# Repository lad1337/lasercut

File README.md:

# Lasercut

PCB and case for an "iso" 72 key mechanical keyboard

## Layout

http://www.keyboard-layout-editor.com/#/gists/ba62eb48125304c6f380ac636846d038

## Case

The case is a sandwich style.
The plates can be rendered at http://builder.swillkb.com/
which is based on https://github.com/swill/kad.

in the case folder you will find a small go app(source) that can achive the same.

prerequisite:
    
    brew install inkscape pstoedit

render:

    cd case
    go run main.go

This will render svg, eps and dxf files.
These can be used with any CAD software.

You will need the following plates:

- 1x switch plate in 1.5mm
- 1x closed with magnets inserts in 3mm (not automatically rendered!!)
- 2x closed in 3mm
- 1x switch in 1.5mm
- 1x open in 3mm
- 1x bottom in 1-3mm

Example render in fusion with stainless steel and brass

## PCB

### Board edge

add the generated `./case/Lasercut_bottom.dxf` to the board and position:

    x: 23.0
    y: 19.94769

TODO: mounting holes

### Netlist

prerequisite: 

- `kle2netlist` installed, see https://github.com/lad1337/kle2netlist
    this will create a netlist from the kle json
- `kicad-kbplacer` kicad plugin installed, see https://github.com/lad1337/kicad-kbplacer
    this is a plugin that will place the swiches to the right place as well as create some tracks
- `node` and `npm install @ijprest/kle-serial --save` 
    this is needed for converting the kle json to its internal format

Steps:

- run:
    `make netlist`
- import the netlist into pcbnew
- run the kicad-kbplacer plugin
- rearrage the controller

    ```
    x: 335.4
    y: 72.6
    roation: 180
    ```
- finish all the other tracks

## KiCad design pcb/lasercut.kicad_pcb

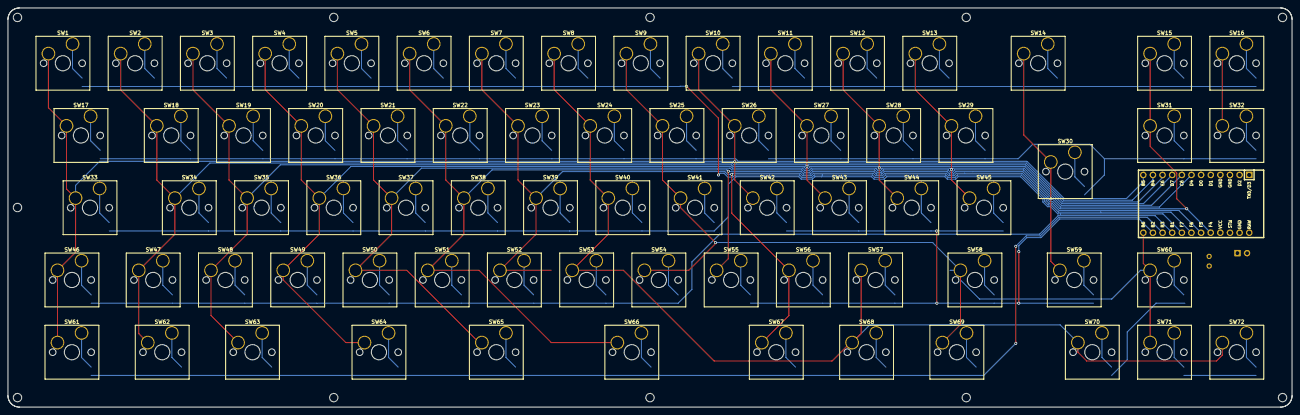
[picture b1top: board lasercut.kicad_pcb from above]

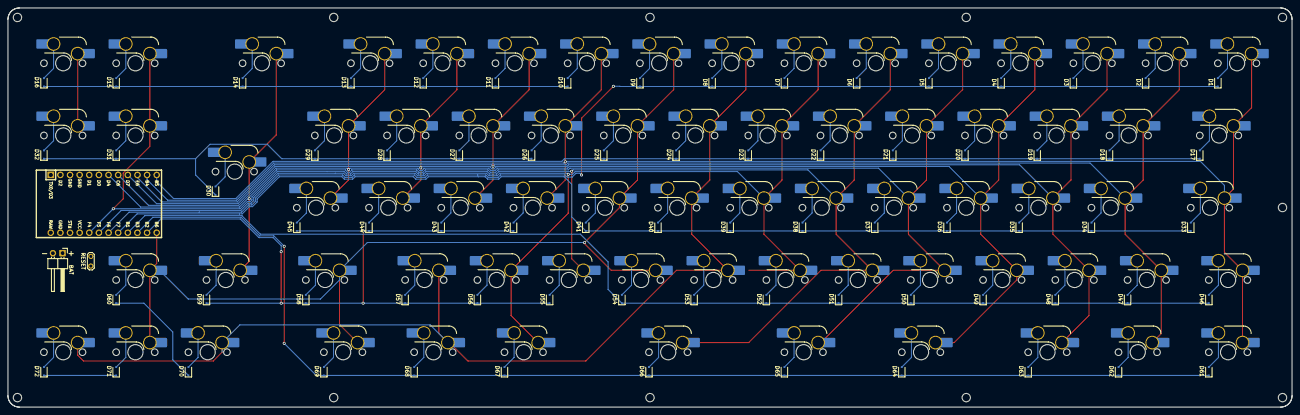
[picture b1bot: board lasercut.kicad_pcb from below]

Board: 2 copper layers, 338.6 x 105.3 mm, 147 parts (74 on the bottom side), 92 nets.

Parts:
BAT: PinHeader_1x02_P2.54mm_Horizontal
D1, D2, D3, D4, D5, D6, D7, D8, D9, D10, D11, D12, D13, D14, D15, D16, D17, D18, D19, D20, D21, D22, D23, D24, D25, D26, D27, D28, D29, D31, D32, D33, D34, D35, D36, D37, D38, D39, D40, D41, D42, D43, D44, D45, D46, D47, D48, D49, D50, D51, D52, D53, D54, D55, D56, D57, D58, D59, D60, D61, D62, D63, D64, D65, D66, D67, D68, D69, D70, D71, D72: 1N4148WS; D_SOD-323F
D30: D; D_SOD-323F
RESET: TestPoint_2Pads_Pitch2.54mm_Drill0.8mm
SW1, SW2, SW3, SW4, SW5, SW6, SW7, SW8, SW9, SW10, SW11, SW12, SW13, SW15, SW16, SW18, SW19, SW20, SW21, SW22, SW23, SW24, SW25, SW26, SW27, SW28, SW29, SW31, SW32, SW34, SW35, SW36, SW37, SW38, SW39, SW40, SW41, SW42, SW43, SW44, SW45, SW47, SW48, SW49, SW50, SW51, SW52, SW53, SW54, SW55, SW56, SW57, SW59, SW60, SW65, SW70, SW71, SW72: SW_Push; SW_Hotswap_Kailh_MX_plated_1.00u
SW14: SW_Push; SW_Hotswap_Kailh_MX_plated_2.00u
SW17: SW_Push; SW_Hotswap_Kailh_MX_plated_1.50u
SW30: SW_Push; SW_Hotswap_Kailh_MX_plated_ISOEnter
SW33, SW58: SW_Push; SW_Hotswap_Kailh_MX_plated_1.75u
SW46, SW61, SW62, SW63, SW67, SW68, SW69: SW_Push; SW_Hotswap_Kailh_MX_plated_1.25u
SW64: SW_Push; SW_Hotswap_Kailh_MX_plated_2.25u
SW66: SW_Push; SW_Hotswap_Kailh_MX_plated_2.75u
U: ProMicro; ArduinoProMicro

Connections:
BAT: BAT.1, U.24
COL0: SW1.1, SW10.1, SW17.1, SW26.1, SW33.1, SW42.1, SW46.1, SW61.1, U.11
COL1: SW2.1, SW11.1, SW18.1, SW27.1, SW34.1, SW43.1, SW47.1, SW62.1, U.10
COL2: SW3.1, SW12.1, SW19.1, SW28.1, SW35.1, SW44.1, SW48.1, SW63.1, U.9
COL3: SW4.1, SW13.1, SW20.1, SW29.1, SW36.1, SW45.1, SW49.1, SW64.1, U.8
COL4: SW5.1, SW14.1, SW21.1, SW30.1, SW37.1, SW50.1, SW59.1, SW65.1, U.7
COL5: SW6.1, SW15.1, SW22.1, SW31.1, SW38.1, SW51.1, SW55.1, SW66.1, U.20
COL6: SW7.1, SW16.1, SW23.1, SW32.1, SW39.1, SW52.1, SW56.1, SW67.1, U.19
COL7: SW8.1, SW24.1, SW40.1, SW53.1, SW57.1, SW68.1, SW70.1, SW72.1, U.2
COL8: SW9.1, SW25.1, SW41.1, SW54.1, SW58.1, SW60.1, SW69.1, SW71.1, U.13
GND: BAT.2, RESET.1, U.3, U.4, U.23
unnamed: D1.2, SW1.2
unnamed: D2.2, SW2.2
unnamed: D3.2, SW3.2
unnamed: D4.2, SW4.2
unnamed: D5.2, SW5.2
unnamed: D6.2, SW6.2
unnamed: D7.2, SW7.2
unnamed: D8.2, SW8.2
unnamed: D9.2, SW9.2
unnamed: D10.2, SW10.2
unnamed: D11.2, SW11.2
unnamed: D12.2, SW12.2
unnamed: D13.2, SW13.2
unnamed: D14.2, SW14.2
unnamed: D15.2, SW15.2
unnamed: D16.2, SW16.2
unnamed: D17.2, SW17.2
unnamed: D18.2, SW18.2
unnamed: D19.2, SW19.2
unnamed: D20.2, SW20.2
unnamed: D21.2, SW21.2
unnamed: D22.2, SW22.2
unnamed: D23.2, SW23.2
unnamed: D24.2, SW24.2
unnamed: D25.2, SW25.2
unnamed: D26.2, SW26.2
unnamed: D27.2, SW27.2
unnamed: D28.2, SW28.2
unnamed: D29.2, SW29.2
unnamed: D30.2, SW30.2
unnamed: D31.2, SW31.2
unnamed: D32.2, SW32.2
unnamed: D33.2, SW33.2
unnamed: D34.2, SW34.2
unnamed: D35.2, SW35.2
unnamed: D36.2, SW36.2
unnamed: D37.2, SW37.2
unnamed: D38.2, SW38.2
unnamed: D39.2, SW39.2
unnamed: D40.2, SW40.2
unnamed: D41.2, SW41.2
unnamed: D42.2, SW42.2
unnamed: D43.2, SW43.2
unnamed: D44.2, SW44.2
unnamed: D45.2, SW45.2
unnamed: D46.2, SW46.2
unnamed: D47.2, SW47.2
unnamed: D48.2, SW48.2
unnamed: D49.2, SW49.2
unnamed: D50.2, SW50.2
unnamed: D51.2, SW51.2
unnamed: D52.2, SW52.2
unnamed: D53.2, SW53.2
unnamed: D54.2, SW54.2
unnamed: D55.2, SW55.2
unnamed: D56.2, SW56.2
unnamed: D57.2, SW57.2
unnamed: D58.2, SW58.2
unnamed: D59.2, SW59.2
unnamed: D60.2, SW60.2
unnamed: D61.2, SW61.2
unnamed: D62.2, SW62.2
unnamed: D63.2, SW63.2
unnamed: D64.2, SW64.2
unnamed: D65.2, SW65.2
unnamed: D66.2, SW66.2
unnamed: D67.2, SW67.2
unnamed: D68.2, SW68.2
unnamed: D69.2, SW69.2
unnamed: D70.2, SW70.2
unnamed: D71.2, SW71.2
unnamed: D72.2, SW72.2
ROW0: D1.1, D2.1, D3.1, D4.1, D5.1, D6.1, D7.1, D8.1, D9.1, U.18
ROW1: D17.1, D18.1, D19.1, D20.1, D21.1, D22.1, D23.1, D24.1, D25.1, U.12
ROW2: D33.1, D34.1, D35.1, D36.1, D37.1, D38.1, D39.1, D40.1, D41.1, U.17
ROW3: D46.1, D47.1, D48.1, D49.1, D50.1, D51.1, D52.1, D53.1, D54.1, U.16
ROW4: D61.1, D62.1, D63.1, D64.1, D65.1, D66.1, D67.1, D68.1, D69.1, U.15
ROW5: D10.1, D11.1, D12.1, D13.1, D14.1, D15.1, D16.1, D60.1, D70.1
ROW6: D26.1, D27.1, D28.1, D29.1, D30.1, D31.1, D32.1, D71.1, D72.1, U.6
ROW7: D42.1, D43.1, D44.1, D45.1, D55.1, D56.1, D57.1, D58.1, D59.1, U.14
RST: RESET.2, U.22

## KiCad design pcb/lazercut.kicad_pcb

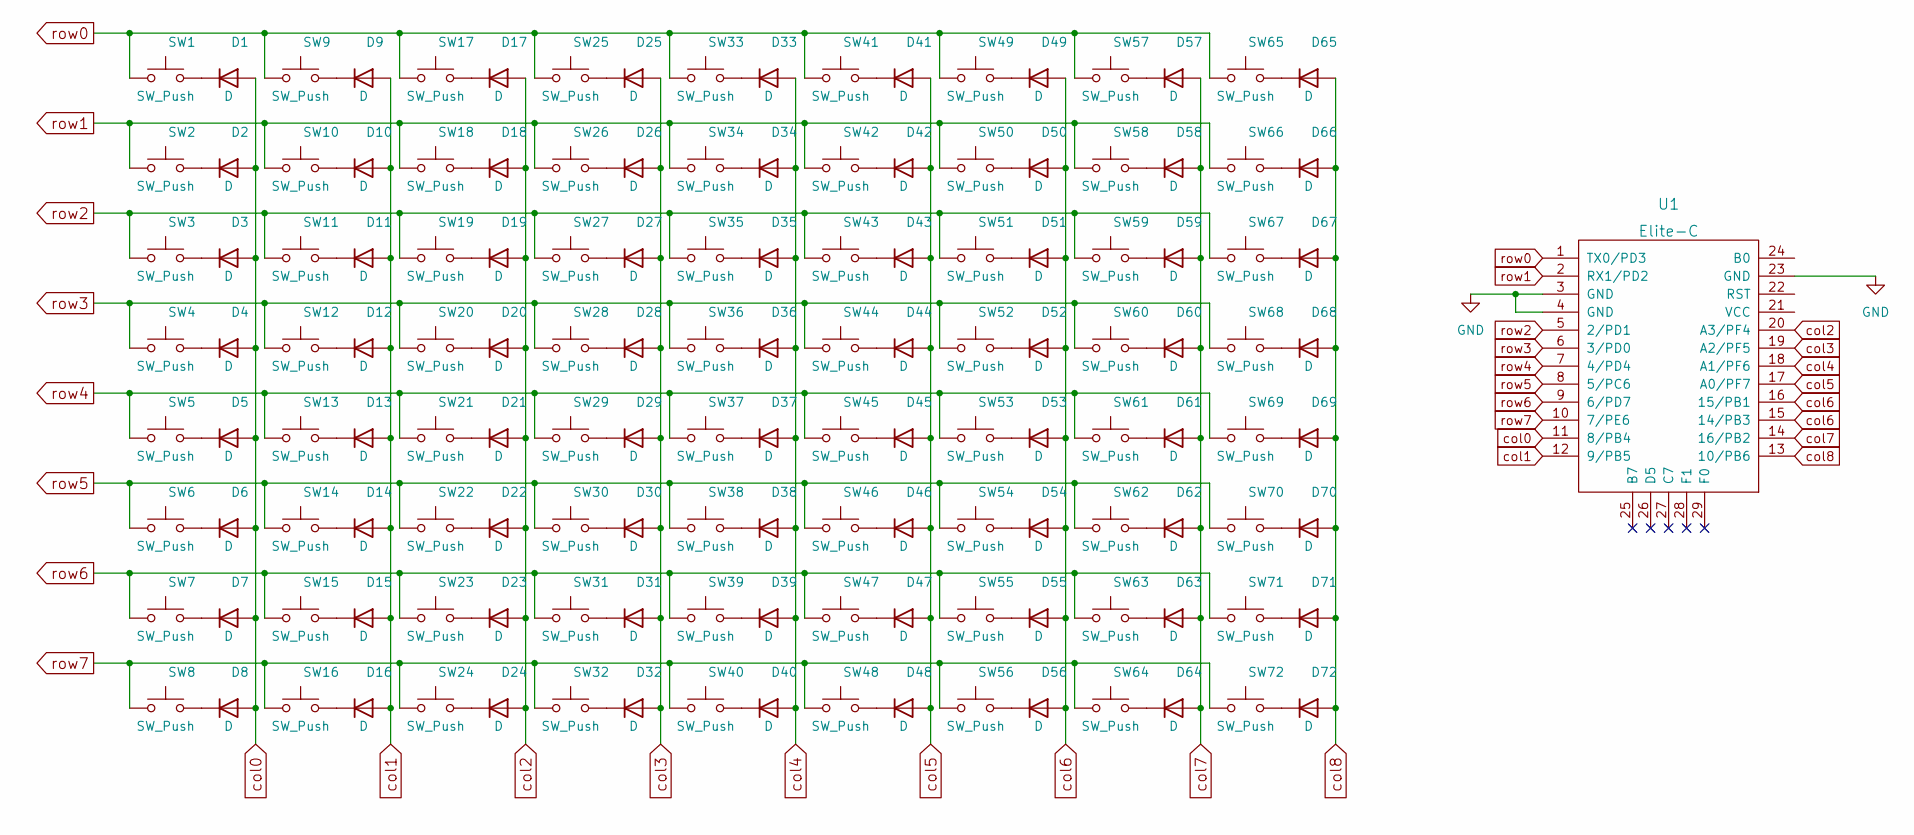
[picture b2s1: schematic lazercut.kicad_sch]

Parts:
D1, D2, D3, D4, D5, D6, D7, D8, D9, D10, D11, D12, D13, D14, D15, D16, D17, D18, D19, D20, D21, D22, D23, D24, D25, D26, D27, D28, D29, D30, D31, D32, D33, D34, D35, D36, D37, D38, D39, D40, D41, D42, D43, D44, D45, D46, D47, D48, D49, D50, D51, D52, D53, D54, D55, D56, D57, D58, D59, D60, D61, D62, D63, D64, D65, D66, D67, D68, D69, D70, D71, D72: D; D_SOD-128
SW1, SW2, SW3, SW4, SW5, SW6, SW7, SW8, SW9, SW10, SW11, SW12, SW13, SW14, SW15, SW16, SW17, SW18, SW19, SW20, SW21, SW22, SW23, SW24, SW25, SW26, SW27, SW28, SW29, SW30, SW31, SW32, SW33, SW34, SW35, SW36, SW37, SW38, SW39, SW40, SW41, SW42, SW43, SW44, SW45, SW46, SW47, SW48, SW49, SW50, SW51, SW52, SW53, SW54, SW55, SW56, SW57, SW58, SW59, SW60, SW61, SW62, SW63, SW64, SW65, SW66, SW67, SW68, SW69, SW70, SW71, SW72: SW_Push; MXOnly-1U-Hotswap-Antishear
U1: Elite-C

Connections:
GND: U1.3 (GND), U1.4 (GND), U1.23 (GND)
unnamed: D1.1 (K), SW1.2
unnamed: D2.1 (K), SW2.2
unnamed: D3.1 (K), SW3.2
unnamed: D4.1 (K), SW4.2
unnamed: D5.1 (K), SW5.2
unnamed: D6.1 (K), SW6.2
unnamed: D7.1 (K), SW7.2
unnamed: D8.1 (K), SW8.2
unnamed: D9.1 (K), SW9.2
unnamed: D10.1 (K), SW10.2
unnamed: D11.1 (K), SW11.2
unnamed: D12.1 (K), SW12.2
unnamed: D13.1 (K), SW13.2
unnamed: D14.1 (K), SW14.2
unnamed: D15.1 (K), SW15.2
unnamed: D16.1 (K), SW16.2
unnamed: D17.1 (K), SW17.2
unnamed: D18.1 (K), SW18.2
unnamed: D19.1 (K), SW19.2
unnamed: D20.1 (K), SW20.2
unnamed: D21.1 (K), SW21.2
unnamed: D22.1 (K), SW22.2
unnamed: D23.1 (K), SW23.2
unnamed: D24.1 (K), SW24.2
unnamed: D25.1 (K), SW25.2
unnamed: D26.1 (K), SW26.2
unnamed: D27.1 (K), SW27.2
unnamed: D28.1 (K), SW28.2
unnamed: D29.1 (K), SW29.2
unnamed: D30.1 (K), SW30.2
unnamed: D31.1 (K), SW31.2
unnamed: D32.1 (K), SW32.2
unnamed: D33.1 (K), SW33.2
unnamed: D34.1 (K), SW34.2
unnamed: D35.1 (K), SW35.2
unnamed: D36.1 (K), SW36.2
unnamed: D37.1 (K), SW37.2
unnamed: D38.1 (K), SW38.2
unnamed: D39.1 (K), SW39.2
unnamed: D40.1 (K), SW40.2
unnamed: D41.1 (K), SW41.2
unnamed: D42.1 (K), SW42.2
unnamed: D43.1 (K), SW43.2
unnamed: D44.1 (K), SW44.2
unnamed: D45.1 (K), SW45.2
unnamed: D46.1 (K), SW46.2
unnamed: D47.1 (K), SW47.2
unnamed: D48.1 (K), SW48.2
unnamed: D49.1 (K), SW49.2
unnamed: D50.1 (K), SW50.2
unnamed: D51.1 (K), SW51.2
unnamed: D52.1 (K), SW52.2
unnamed: D53.1 (K), SW53.2
unnamed: D54.1 (K), SW54.2
unnamed: D55.1 (K), SW55.2
unnamed: D56.1 (K), SW56.2
unnamed: D57.1 (K), SW57.2
unnamed: D58.1 (K), SW58.2
unnamed: D59.1 (K), SW59.2
unnamed: D60.1 (K), SW60.2
unnamed: D61.1 (K), SW61.2
unnamed: D62.1 (K), SW62.2
unnamed: D63.1 (K), SW63.2
unnamed: D64.1 (K), SW64.2
unnamed: D65.1 (K), SW65.2
unnamed: D66.1 (K), SW66.2
unnamed: D67.1 (K), SW67.2
unnamed: D68.1 (K), SW68.2
unnamed: D69.1 (K), SW69.2
unnamed: D70.1 (K), SW70.2
unnamed: D71.1 (K), SW71.2
unnamed: D72.1 (K), SW72.2
col0: D1.2 (A), D2.2 (A), D3.2 (A), D4.2 (A), D5.2 (A), D6.2 (A), D7.2 (A), D8.2 (A), U1.11 (8/PB4)
col1: D9.2 (A), D10.2 (A), D11.2 (A), D12.2 (A), D13.2 (A), D14.2 (A), D15.2 (A), D16.2 (A), U1.12 (9/PB5)
col2: D17.2 (A), D18.2 (A), D19.2 (A), D20.2 (A), D21.2 (A), D22.2 (A), D23.2 (A), D24.2 (A), U1.20 (A3/PF4)
col3: D25.2 (A), D26.2 (A), D27.2 (A), D28.2 (A), D29.2 (A), D30.2 (A), D31.2 (A), D32.2 (A), U1.19 (A2/PF5)
col4: D33.2 (A), D34.2 (A), D35.2 (A), D36.2 (A), D37.2 (A), D38.2 (A), D39.2 (A), D40.2 (A), U1.18 (A1/PF6)
col5: D41.2 (A), D42.2 (A), D43.2 (A), D44.2 (A), D45.2 (A), D46.2 (A), D47.2 (A), D48.2 (A), U1.17 (A0/PF7)
col6: D49.2 (A), D50.2 (A), D51.2 (A), D52.2 (A), D53.2 (A), D54.2 (A), D55.2 (A), D56.2 (A), U1.15 (14/PB3), U1.16 (15/PB1)
col7: D57.2 (A), D58.2 (A), D59.2 (A), D60.2 (A), D61.2 (A), D62.2 (A), D63.2 (A), D64.2 (A), U1.14 (16/PB2)
col8: D65.2 (A), D66.2 (A), D67.2 (A), D68.2 (A), D69.2 (A), D70.2 (A), D71.2 (A), D72.2 (A), U1.13 (10/PB6)
row0: SW1.1, SW9.1, SW17.1, SW25.1, SW33.1, SW41.1, SW49.1, SW57.1, SW65.1, U1.1 (TX0/PD3)
row1: SW2.1, SW10.1, SW18.1, SW26.1, SW34.1, SW42.1, SW50.1, SW58.1, SW66.1, U1.2 (RX1/PD2)
row2: SW3.1, SW11.1, SW19.1, SW27.1, SW35.1, SW43.1, SW51.1, SW59.1, SW67.1, U1.5 (2/PD1)
row3: SW4.1, SW12.1, SW20.1, SW28.1, SW36.1, SW44.1, SW52.1, SW60.1, SW68.1, U1.6 (3/PD0)
row4: SW5.1, SW13.1, SW21.1, SW29.1, SW37.1, SW45.1, SW53.1, SW61.1, SW69.1, U1.7 (4/PD4)
row5: SW6.1, SW14.1, SW22.1, SW30.1, SW38.1, SW46.1, SW54.1, SW62.1, SW70.1, U1.8 (5/PC6)
row6: SW7.1, SW15.1, SW23.1, SW31.1, SW39.1, SW47.1, SW55.1, SW63.1, SW71.1, U1.9 (6/PD7)
row7: SW8.1, SW16.1, SW24.1, SW32.1, SW40.1, SW48.1, SW56.1, SW64.1, SW72.1, U1.10 (7/PE6)

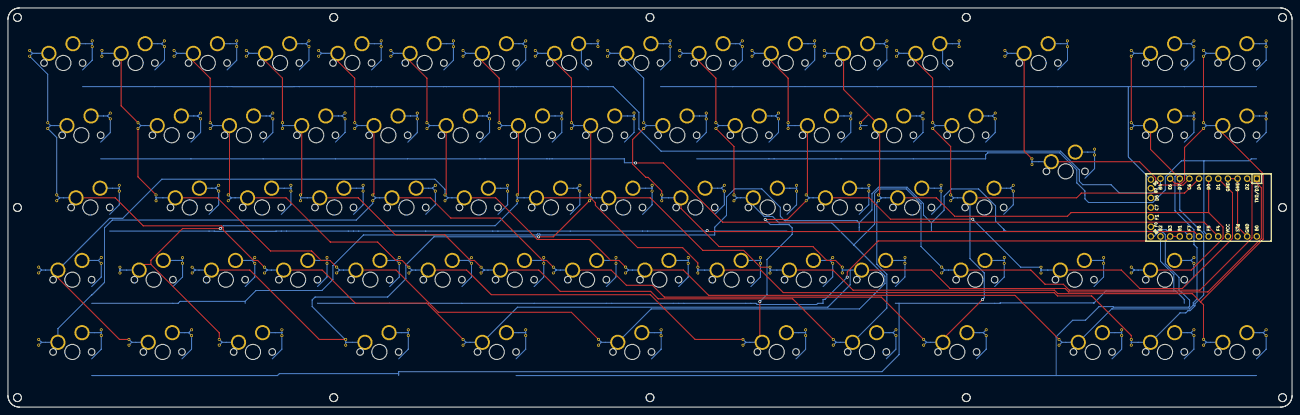
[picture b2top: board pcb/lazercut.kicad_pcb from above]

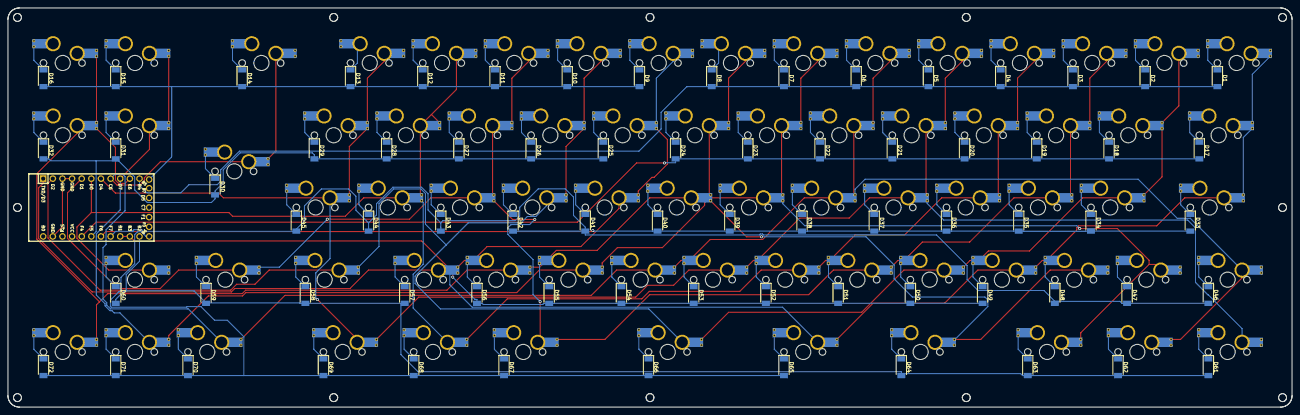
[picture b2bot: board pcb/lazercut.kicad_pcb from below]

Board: 2 copper layers, 338.6 x 105.3 mm, 145 parts (72 on the bottom side), 90 nets.

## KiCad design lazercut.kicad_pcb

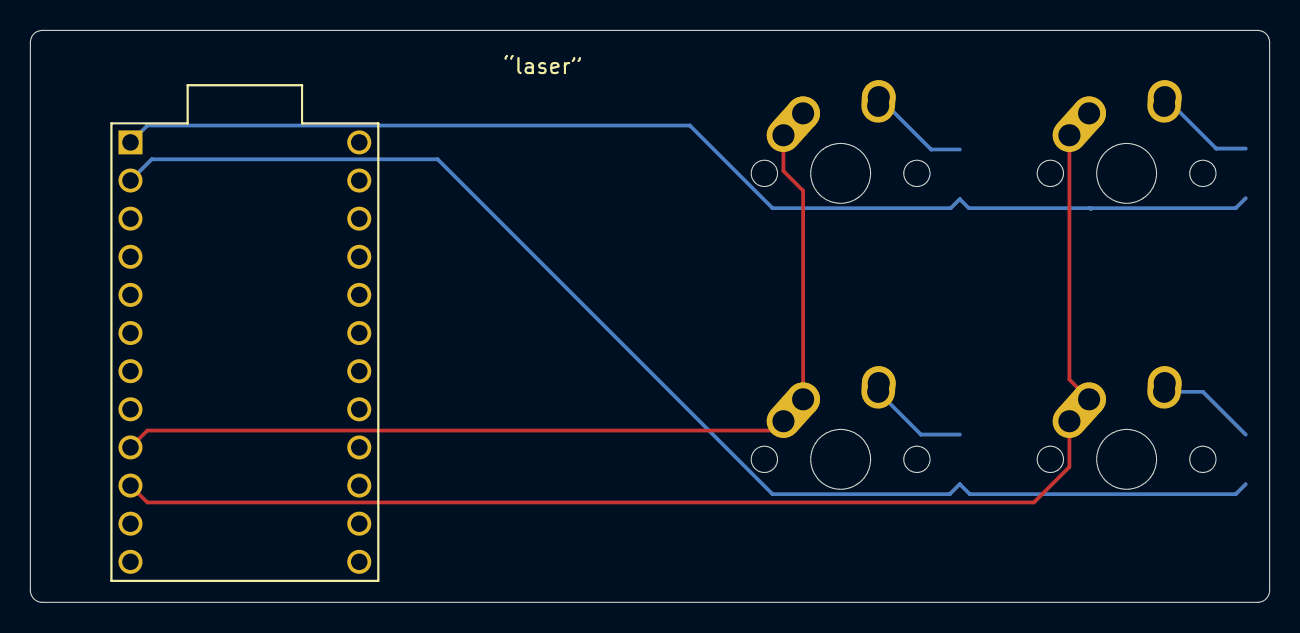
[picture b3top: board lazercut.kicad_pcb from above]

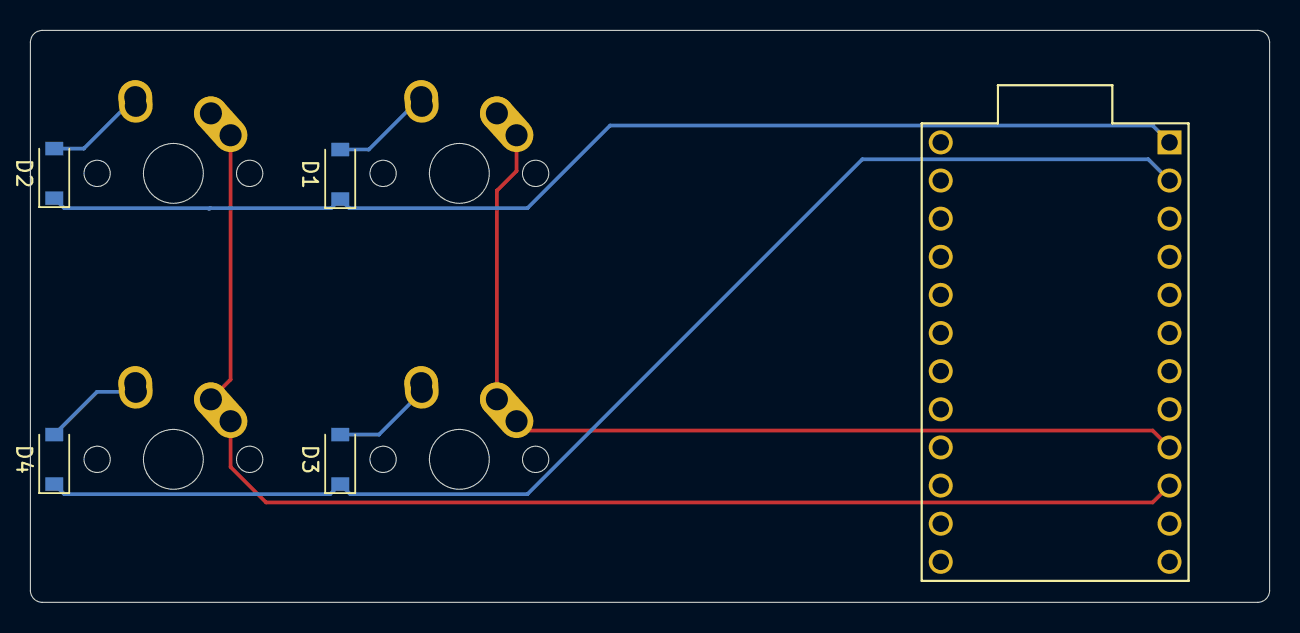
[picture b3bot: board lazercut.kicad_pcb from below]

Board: 2 copper layers, 82.6 x 38.1 mm, 9 parts (4 on the bottom side), 9 nets.

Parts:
D1, D2, D3, D4: D_Small; D_SOD-123
MX1, MX2, MX3, MX4: MX-NoLED; MX-1U-NoLED
U1: ProMicro

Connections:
Col0: MX1.1, MX3.1, U1.9
Col1: MX2.1, MX4.1, U1.10
GND: U1.3, U1.4, U1.23
unnamed: D1.2, MX1.2
unnamed: D2.2, MX2.2
unnamed: D3.2, MX3.2
unnamed: D4.2, MX4.2
Row0: D1.1, D2.1, U1.1
Row1: D3.1, D4.1, U1.2

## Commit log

2021-10-08 initial setup
2021-10-08 finished tutorial
2021-10-26 nuke ... restating the project
2021-11-29 a new hope
2022-01-27 only split space with color
2022-01-27 add readme
2022-01-27 cleaning
2022-01-28 add case render app and add rendered image
2022-01-28 full render
2022-01-28 add new renders
2022-01-28 more to read
2022-03-05 re do pcb aligment and traceing
2022-03-05 reposition elite-c because of outer frame
2022-03-06 add gerber and more images
2022-03-06 cleaning repo a little
2022-03-06 add batter headers
2022-03-07 new freerouting version
    need to redo the matrix/switch position
2022-03-14 cleanup and makefile with some tools
2022-03-14 new pcb kicad project
2022-03-14 add kicad parts library modules
2022-03-14 add kicad cache files ... not sure if this is cool
2022-03-14 add battery connector and images
2022-03-14 update layout image
2022-03-14 add gerber files
2022-03-14 update readme with pcb instructions
2022-03-15 FIX: Row5 was connected to GND
2022-04-03 90% re routed
2022-04-21 add script to generate QMK layout macro
